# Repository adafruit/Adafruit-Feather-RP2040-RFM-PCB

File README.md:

## Adafruit Feather RP2040 RFM PCB

<a href="http://www.adafruit.com/products/5712"><br/>
<a href="http://www.adafruit.com/products/5714"><br/>
Click here to purchase one from the Adafruit shop</a>

PCB files for the Adafruit Feather RP2040 RFM69 and RFM9x. The board files are identical for both
types of radio modules!

Format is EagleCAD schematic and board layout
* https://www.adafruit.com/product/5712

### Description

This is the Adafruit Feather RP2040 RFM. We call these RadioFruits, our take on a microcontroller with packet radio transceiver with built-in USB and battery charging. It's an Adafruit Feather RP2040 with a radio module cooked in! Great for making wireless networks that are more flexible than Bluetooth LE and without the high power requirements of WiFi.

Feather is the development board specification from Adafruit, and like its namesake, it is thin, light, and lets you fly! We designed Feather to be a new standard for portable microcontroller cores. We have other boards in the Feather family, check'em out here.

It's kinda like we took our RP2040 Feather and an RFM breakout board and glued them together. You get all the pins for use on the Feather, the Lipoly battery support, USB C power / data, onboard NeoPixel, 8MB of FLASH for storing code and files, and then with the 8 unused pins, we wired up all the DIO pins on the RFM module. There's even room left over for a STEMMA QT connector an a uFL connector for connecting larger antennas.

At the Feather's heart is an RP2040 chip, clocked at 133 MHz and at 3.3V logic, the same one used in the Raspberry Pi Pico. This chip has a whopping 8MB of onboard QSPI FLASH and 264K of RAM! This makes it great for making wireless sensor nodes that can send to each other without a lot of software configuration.

To make it easy to use for portable projects, we added a connector for any of our 3.7V Lithium polymer batteries and built-in battery charging. You don't need a battery, it will run just fine straight from the USB Type C connector. But, if you do have a battery, you can take it on the go, then plug in the USB to recharge. The Feather will automatically switch over to USB power when its available.

Here're some handy specs! You get:
* Measures approximately 2.0" x 0.9" x 0.28" (50.8mm x 22.8mm x 7mm) without headers soldered in
* Light as a (large?) feather - approximately 6 grams
* RP2040 32-bit Cortex M0+ dual core running at ~133 MHz @ 3.3V logic and power
* 264 KB RAM
* 8 MB SPI FLASH chip for storing files and CircuitPython/MicroPython code storage. No EEPROM
* Tons of GPIO! 21 x GPIO pins with following capabilities:
* Four 12-bit ADCs (one more than Pico)
* Two I2C, Two SPI, and two UART peripherals, we label one for the 'main' interface in standard Feather locations
* 16 x PWM outputs - for servos, LEDs, etc
* Built-in 200mA+ lipoly charger with charging status indicator LED
* Pin #13 red LED for general purpose blinking
* RGB NeoPixel for full-color indication.
* On-board STEMMA QT connector that lets you quickly connect any Qwiic, STEMMA QT or Grove I2C devices with no soldering!
* Both Reset button and Bootloader select button for quick restarts (no unplugging-replugging to relaunch code)
* USB Type C connector lets you access built-in ROM USB bootloader and serial port debugging
* 3.3V Power/enable pin
* 4 mounting holes
* 12 MHz crystal for perfect timing.
* 3.3V regulator with 500mA peak current output

We squished all the parts on our Feather RP2040 over towards the USB port to make some room on the end. This Feather RFM uses the extra space left over to add an RFM radio module. These radios are not good for transmitting audio or video, but they do work quite well for small data packet transmission when you need more range than 2.4 GHz (BT, BLE, WiFi, ZigBee).

Radio module specifications:

* SX1231 or SX127x LoRa® based module with SPI interface
* +13 to +20 dBm up to 100 mW Power Output Capability (power output selectable in software)
* 50mA (+13 dBm) to 150mA (+20dBm) current draw for transmissions, ~30mA during active radio listening.
* Range of approx. 500 meters to 2Km, depending on which RFM module, as well as obstructions, frequency, antenna and power output
* Create multipoint networks with individual node addresses
* Encrypted packet engine with AES-128
* Packet/LoRa radio with ready-to-go Arduino & CircuitPython libraries
* Uses the license-free ISM bands (ITU "Europe" @ 433MHz and ITU "Americas" @ 900MHz)
* Simple wire antenna can be soldered into a solder pad, there's also a uFL connector that can be used with uFL-to-SMA adapters for attaching bigger antennas.

* Comes fully assembled and tested, we also toss in some headers so you can solder it in and plug into a solderless breadboard. You will need to cut and solder on a small piece of wire (any solid or stranded core is fine) in order to create your antenna. or use a uFL connector and an appropriate SMA antenna. Lipoly battery and USB cable are not included, but we do have lots of options in the shop if you'd like!

### License

Adafruit invests time and resources providing this open source design, please support Adafruit and open-source hardware by purchasing products from [Adafruit](https://www.adafruit.com)!

Designed by Limor Fried/Ladyada for Adafruit Industries.

Creative Commons Attribution/Share-Alike, all text above must be included in any redistribution. 
See license.txt for additional details.

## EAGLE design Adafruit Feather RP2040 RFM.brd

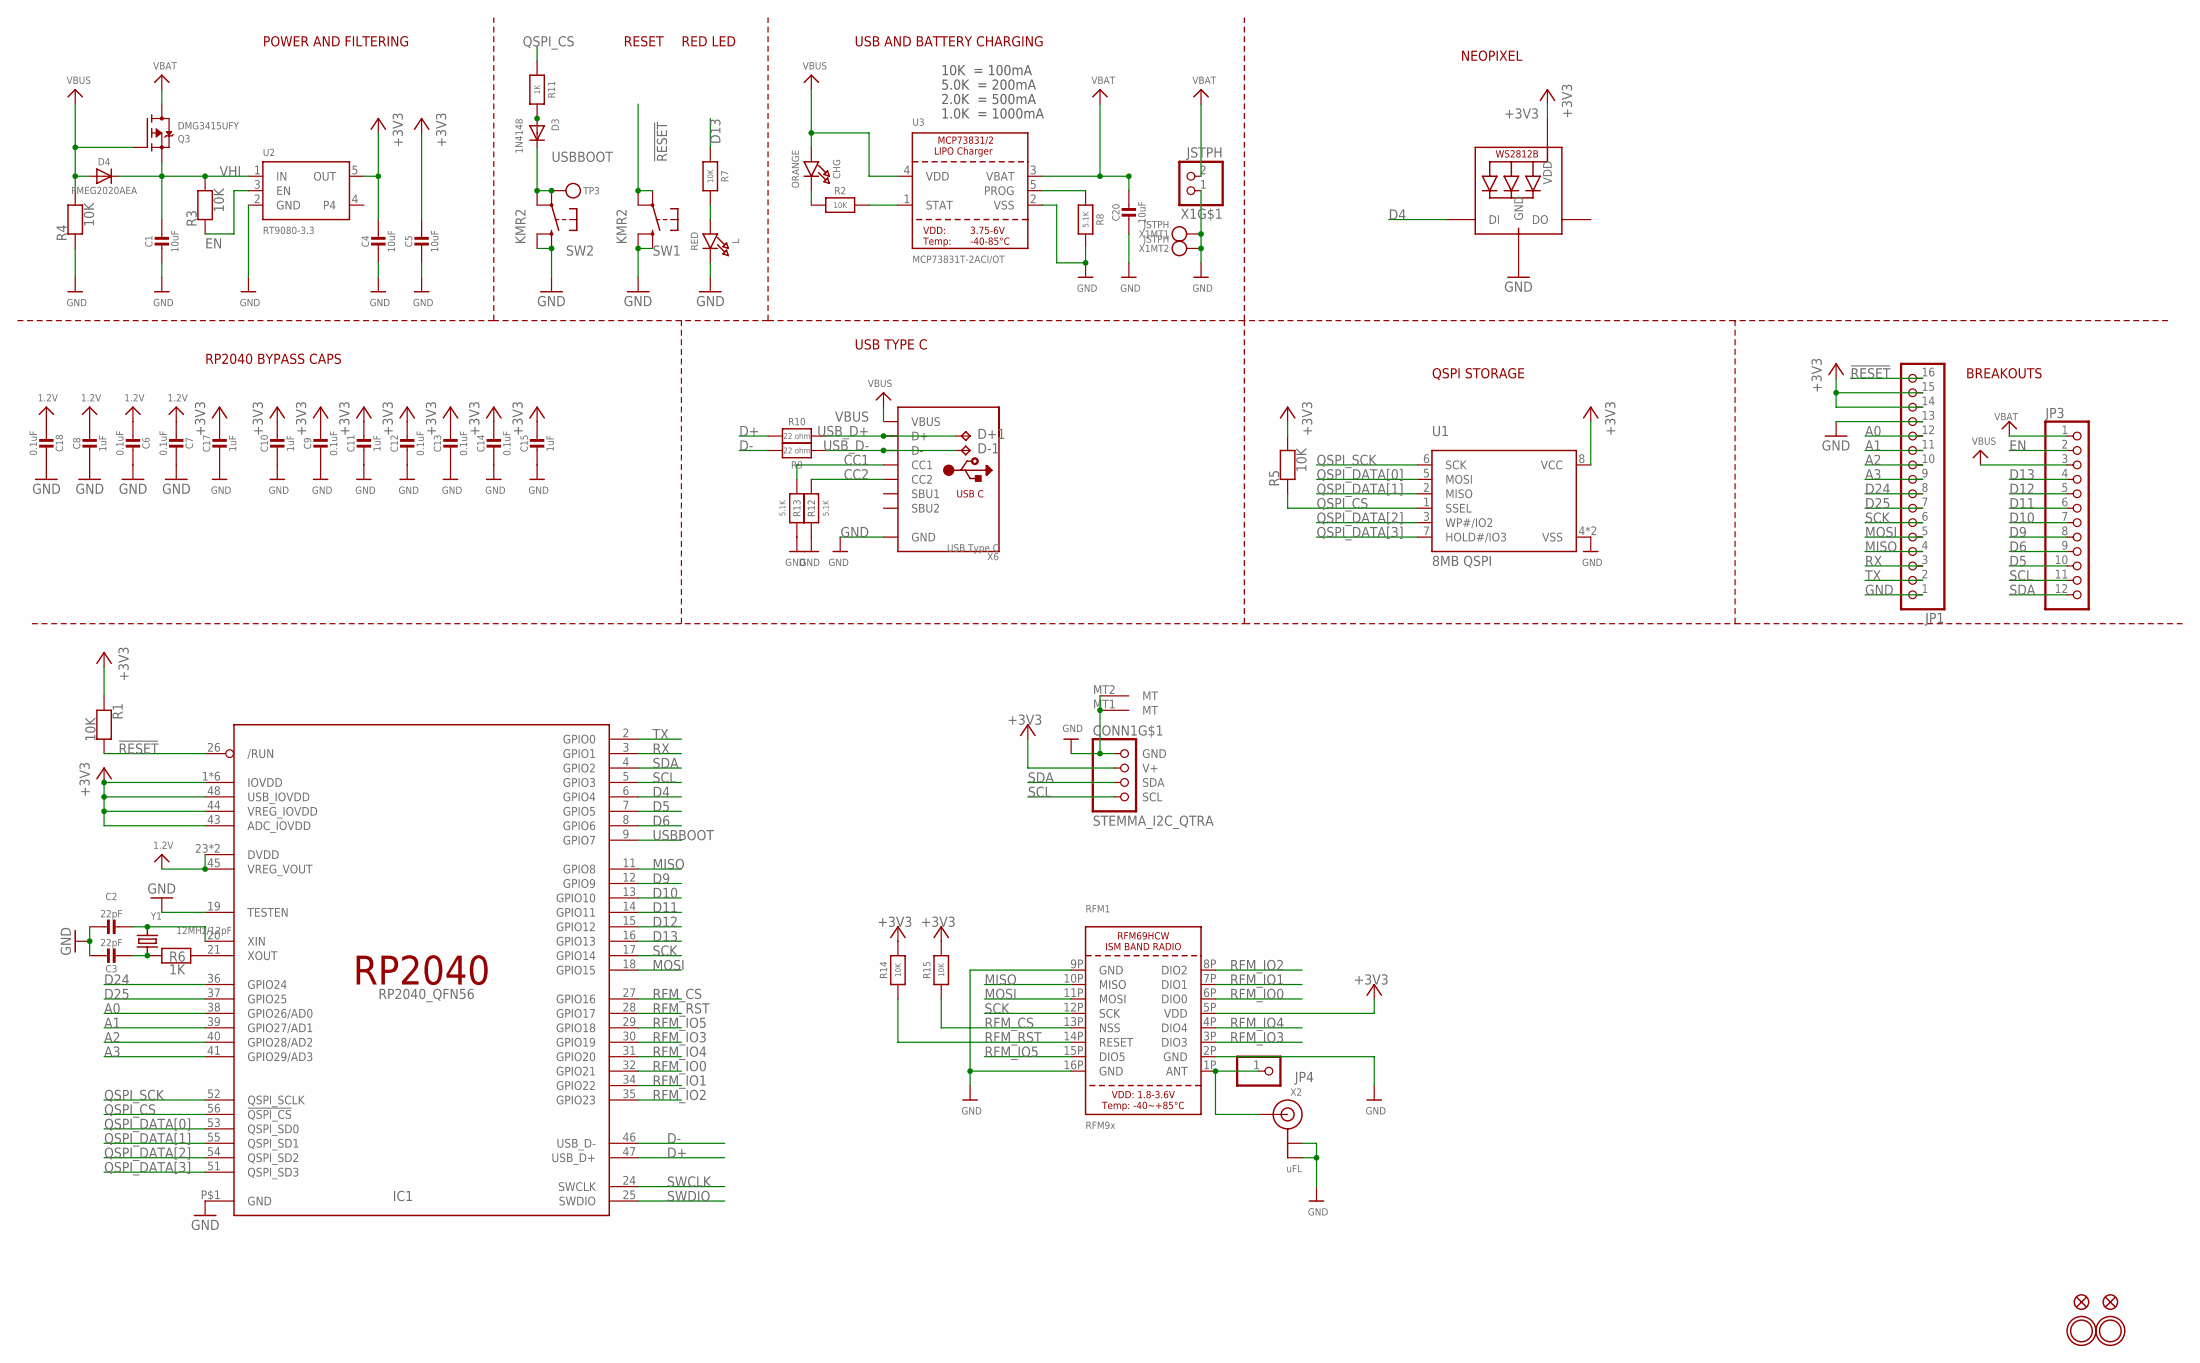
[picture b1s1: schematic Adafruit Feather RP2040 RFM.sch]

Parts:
C1, C4, C5, C20: 10uF; 0805-NO
C2, C3: 22pF; _0402NO
C6, C7, C9, C12, C13, C14, C18: 0.1uF; _0402NO
C8, C10, C11, C15, C17: 1uF; _0402NO
CHG: ORANGE; CHIPLED_0603_NOOUTLINE
CONN1: STEMMA_I2C_QTRA; JST_SH4_RA
D3: 1N4148; SOD-323F
D4: PMEG2020AEA; SOD-323F
D+1: TPB1,27; B1,27
D-1: TPB1,27; B1,27
IC1: RP2040_QFN56; QFN56_7MM_REDUCEDEPAD
JP1: HEADER-1X16ROUND; 1X16_ROUND
JP3: HEADER-1X12; 1X12_ROUND
JP4: HEADER-1X1ROUND; 1X01_ROUND
L: RED; CHIPLED_0603_NOOUTLINE
LED1: WS2812B_SK6805_1515; SK6805_1515
Q3: DMG3415UFY; DFN2015-3
R1, R2, R3, R4, R5, R7, R14, R15: 10K; _0402NO
R6, R11: 1K; _0402NO
R8, R12, R13: 5.1K; _0402NO
R9, R10: 22 ohm; _0402NO
RFM1: RFM9x; RFMHCW_SMT
SW1, SW2: KMR2; BTN_RKB2_4.6X2.8
TP3: TESTPOINTROUND1.5MMNO; TESTPOINT_ROUND_1.5MM_NO
U1: 8MB QSPI; USON8_4X4
U2: RT9080-3.3; SOT23-5; JLC_ROTATION 0
U3: MCP73831T-2ACI/OT; SOT23-5
U$31, U$32: MOUNTINGHOLE2.5; MOUNTINGHOLE_2.5_PLATED
U$34, U$35: FIDUCIAL_1MM
X1: JSTPH; JSTPH2_BATT
X2: uFL; U.FL
X6: USB Type C; USB_C_CUSB31-CFM2AX-01-X
Y1: 12MHz/12pF; CRYSTAL_2.5X2

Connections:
1.2V: C6.2, C7.2, C8.1, C18.2, IC1.23 (DVDD), IC1.45 (VREG_VOUT), IC1.50 (DVDD)
!RESET: IC1.26 (/RUN), JP1.16, R1.2, SW1.A, SW1.A' (P1)
+3V3: C4.1, C5.1, C9.1, C10.1, C11.1, C12.1, C13.1, C14.1, C15.1, C17.1, CONN1.2 (V+), IC1.1 (IOVDD), IC1.10 (IOVDD), IC1.22 (IOVDD), IC1.33 (IOVDD), IC1.42 (IOVDD), IC1.43 (ADC_IOVDD), IC1.44 (VREG_IOVDD), IC1.48 (USB_IOVDD), IC1.49 (IOVDD), JP1.14, JP1.15, LED1.2 (VDD), R1.1, R5.2, R14.2, R15.2, RFM1.5P (VDD), U1.8 (VCC), U2.5 (OUT)
A0: IC1.38 (GPIO26/AD0), JP1.12
A1: IC1.39 (GPIO27/AD1), JP1.11
A2: IC1.40 (GPIO28/AD2), JP1.10
A3: IC1.41 (GPIO29/AD3), JP1.9
CC1: R13.2, X6.A5 (CC1)
CC2: R12.2, X6.B5 (CC2)
D4: IC1.6 (GPIO4), LED1.1 (DI)
D5: IC1.7 (GPIO5), JP3.10
D6: IC1.8 (GPIO6), JP3.9
D9: IC1.12 (GPIO9), JP3.8
D10: IC1.13 (GPIO10), JP3.7
D11: IC1.14 (GPIO11), JP3.6
D12: IC1.15 (GPIO12), JP3.5
D13: IC1.16 (GPIO13), JP3.4, R7.1
D24: IC1.36 (GPIO24), JP1.8
D25: IC1.37 (GPIO25), JP1.7
D+: IC1.47 (USB_D+), R10.2
D-: IC1.46 (USB_D-), R9.2
EN: JP3.2, R3.1, U2.3 (EN)
GND: C1.2, C2.1, C3.1, C4.2, C5.2, C6.1, C7.1, C8.2, C9.2, C10.2, C11.2, C12.2, C13.2, C14.2, C15.2, C17.2, C18.1, C20.2, CONN1.1 (GND), CONN1.MT1 (MT), CONN1.MT2 (MT), IC1.19 (TESTEN), IC1.P$1 (GND), JP1.1, JP1.13, L.C, LED1.4 (GND), R4.1, R8.2, R12.1, R13.1, RFM1.2P (GND), RFM1.9P (GND), RFM1.16P (GND), SW1.B (S), SW1.B' (S1), SW2.B (S), SW2.B' (S1), U1.4 (VSS), U1.PAD (VSS), U2.2 (GND), U3.2 (VSS), X1.1, X1.NC1, X1.NC2, X2.1 (GND), X2.2 (GND), X6.A1B12 (GND), X6.B1A12 (GND)
MISO: IC1.11 (GPIO8), JP1.4, RFM1.10P (MISO)
MOSI: IC1.18 (GPIO15), JP1.5, RFM1.11P (MOSI)
unnamed: CHG.C, R2.1
unnamed: L.A, R7.2
unnamed: R2.2, U3.1 (STAT)
unnamed: R8.1, U3.5 (PROG)
unnamed: C2.2, IC1.20 (XIN), Y1.3 (2)
unnamed: C3.2, R6.1, Y1.1
unnamed: IC1.21 (XOUT), R6.2
unnamed: D3.A, R11.2
QSPI_CS: IC1.56 (!QSPI_CS), R5.1, R11.1, U1.1 (SSEL)
QSPI_DATA[0]: IC1.53 (QSPI_SD0), U1.5 (MOSI)
QSPI_DATA[1]: IC1.55 (QSPI_SD1), U1.2 (MISO)
QSPI_DATA[2]: IC1.54 (QSPI_SD2), U1.3 (WP#/IO2)
QSPI_DATA[3]: IC1.51 (QSPI_SD3), U1.7 (HOLD#/IO3)
QSPI_SCK: IC1.52 (QSPI_SCLK), U1.6 (SCK)
RFM_CS: IC1.27 (GPIO16), R15.1, RFM1.13P (NSS)
RFM_IO0: IC1.32 (GPIO21), RFM1.6P (DIO0)
RFM_IO1: IC1.34 (GPIO22), RFM1.7P (DIO1)
RFM_IO2: IC1.35 (GPIO23), RFM1.8P (DIO2)
RFM_IO3: IC1.30 (GPIO19), RFM1.3P (DIO3)
RFM_IO4: IC1.31 (GPIO20), RFM1.4P (DIO4)
RFM_IO5: IC1.29 (GPIO18), RFM1.15P (DIO5)
RFM_RST: IC1.28 (GPIO17), R14.1, RFM1.14P (RESET)
RFOUT: JP4.1, RFM1.1P (ANT), X2.3 (SIGNAL)
RX: IC1.3 (GPIO1), JP1.3
SCK: IC1.17 (GPIO14), JP1.6, RFM1.12P (SCK)
SCL: CONN1.4 (SCL), IC1.5 (GPIO3), JP3.11
SDA: CONN1.3 (SDA), IC1.4 (GPIO2), JP3.12
SWCLK: IC1.24 (SWCLK)
SWDIO: IC1.25 (SWDIO)
TX: IC1.2 (GPIO0), JP1.2
USBBOOT: D3.C, IC1.9 (GPIO7), SW2.A, SW2.A' (P1), TP3.P$1
USB_D+: D+1.TP, R10.1, X6.A6 (D+), X6.B6 (D+)
USB_D-: D-1.TP, R9.1, X6.A7 (D-), X6.B7 (D-)
VBAT: C20.1, JP3.1, Q3.3 (D), U3.3 (VBAT), X1.2
VBUS: CHG.A, D4.A, JP3.3, Q3.1 (G), R4.2, U3.4 (VDD), X6.A4B9 (VBUS), X6.B4A9 (VBUS)
VHI: C1.1, D4.C, Q3.2 (S), R3.2, U2.1 (IN)

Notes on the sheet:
POWER AND FILTERING
RESET
10K = 100mA
5.0K = 200mA
2.0K = 500mA
1.0K = 1000mA
USB AND BATTERY CHARGING
BREAKOUTS
RED LED
RP2040 BYPASS CAPS
USB TYPE C
QSPI STORAGE
NEOPIXEL

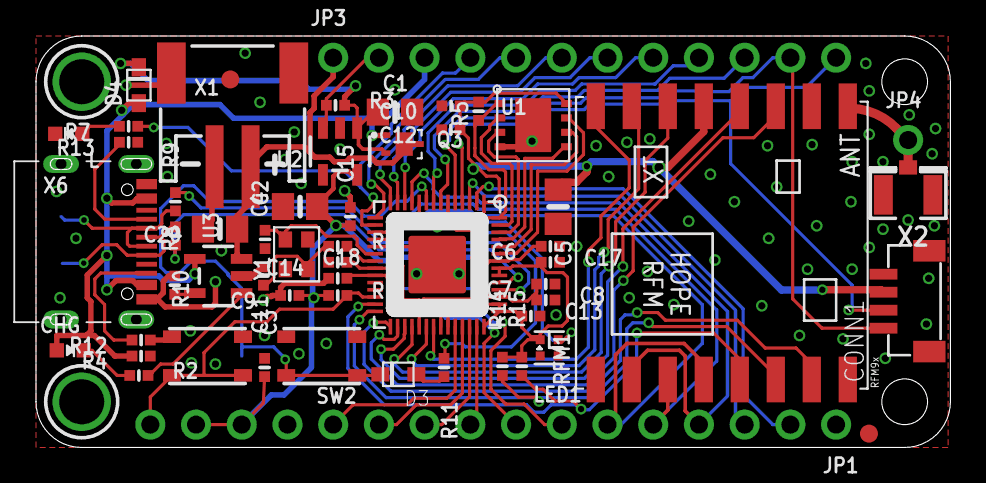
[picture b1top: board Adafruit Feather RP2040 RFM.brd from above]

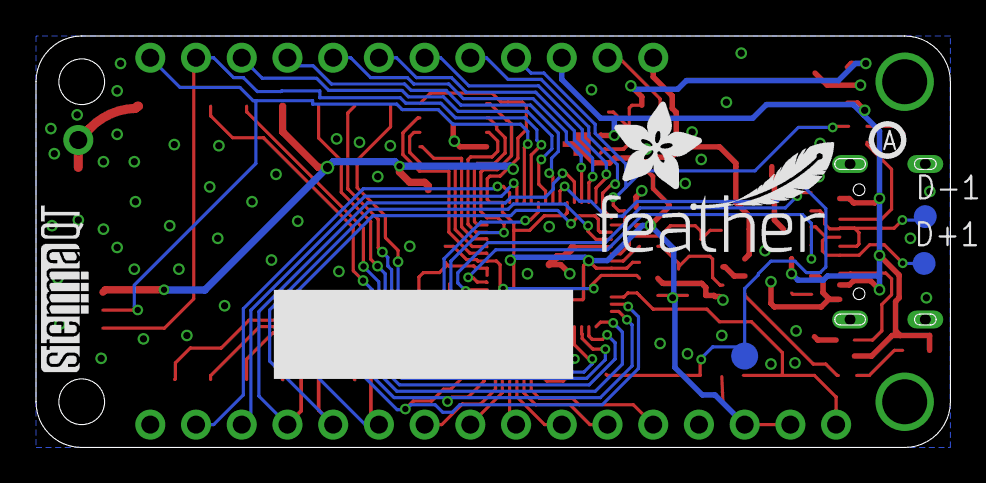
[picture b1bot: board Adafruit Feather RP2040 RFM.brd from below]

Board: 2 copper layers, 50.8 x 22.9 mm, 120 parts (39 on the bottom side), 59 nets.

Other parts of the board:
PLABEL0: PLABEL0
PLABEL1: PLABEL1
PLABEL2: PLABEL2
PLABEL3: PLABEL3
PLABEL4: PLABEL4
PLABEL5: PLABEL5
PLABEL6: PLABEL6
PLABEL7: PLABEL7
PLABEL8: PLABEL8
PLABEL9: PLABEL9
PLABEL10: PLABEL10
PLABEL11: PLABEL11
PLABEL12: PLABEL12
PLABEL13: PLABEL13
PLABEL14: PLABEL14
PLABEL15: PLABEL15
PLABEL16: PLABEL16
PLABEL17: PLABEL17
PLABEL18: PLABEL18
PLABEL19: PLABEL19
PLABEL20: PLABEL20
PLABEL21: PLABEL21
PLABEL22: PLABEL22
PLABEL23: PLABEL23
PLABEL24, PLABEL54: PLABEL24
PLABEL25: PLABEL25
PLABEL26: PLABEL26
PLABEL27: PLABEL27
PLABEL28: PLABEL28
PLABEL29: PLABEL29
PLABEL30: PLABEL30
PLABEL31: PLABEL31
PLABEL32: PLABEL32
PLABEL33: PLABEL33
PLABEL34: PLABEL34
PLABEL35: PLABEL35
PLABEL36: PLABEL36
PLABEL37: PLABEL37
PLABEL38: PLABEL38
PLABEL39: PLABEL39
PLABEL40: PLABEL40
PLABEL41: PLABEL41
PLABEL42: PLABEL42
PLABEL43: PLABEL43
PLABEL44: PLABEL44
PLABEL45: PLABEL45
PLABEL46: PLABEL46
PLABEL47: PLABEL47
PLABEL48: PLABEL48
PLABEL49: PLABEL49
PLABEL51: PLABEL51
PLABEL52: PLABEL52
PLABEL53: PLABEL53
PLABEL540: PLABEL540
U$13: PCBFEAT-REV-040
U$45: ADAFRUIT_5MM
U$46: STEMMAQT
U$47: FEATHERLOGO_SMALL

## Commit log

2023-04-03 Add board files.
2023-04-03 Add PrettyPins
2023-04-05 Add factory reset file.
2023-05-03 Add RFM9x factory reset file
2025-09-24 Add revised prettypins
    Fixes battery JST view

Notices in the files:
parts and their libraries:
microbuilder: This work is placed in the public domain, and may be freely used for commercial and non-commercial work with the following conditions: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
